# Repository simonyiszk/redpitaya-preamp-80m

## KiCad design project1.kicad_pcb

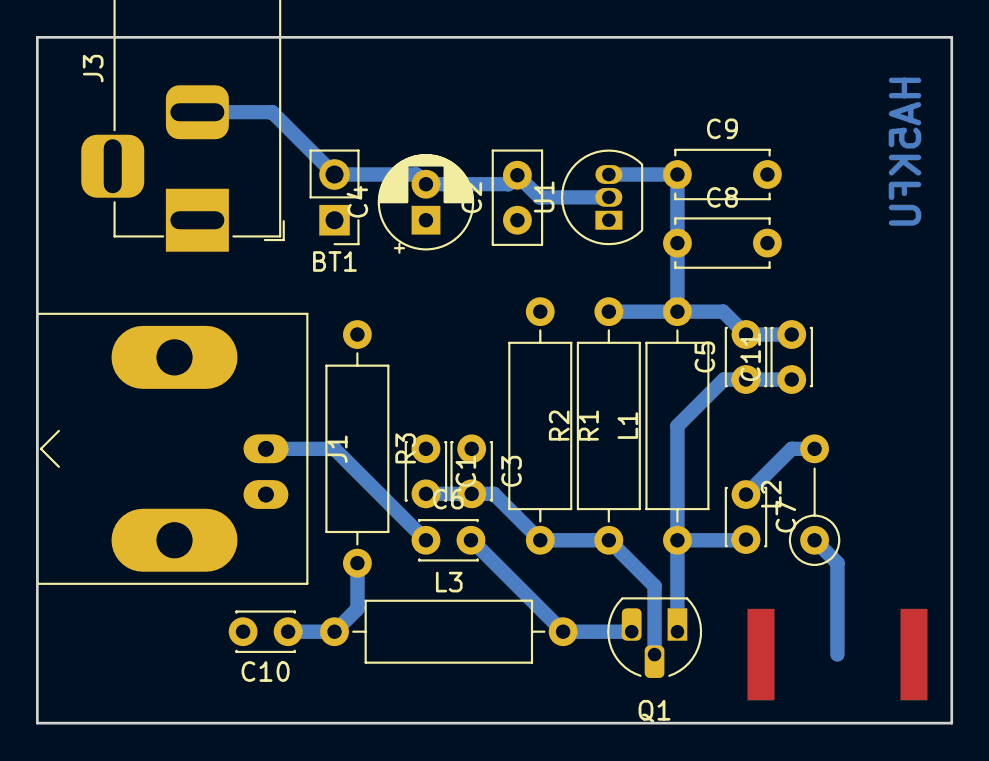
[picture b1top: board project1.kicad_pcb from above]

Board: 2 copper layers, 50.8 x 38.1 mm, 23 parts (1 on the bottom side), 10 nets.

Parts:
BT1: Battery_Cell; PinHeader_1x02_P2.54mm_Vertical
C1, C3, C6, C7: 8n2; C_Disc_D3.0mm_W2.0mm_P2.50mm
C2: 100n; C_Disc_D5.0mm_W2.5mm_P2.50mm
C4: 10u; CP_Radial_D5.0mm_P2.00mm
C5: 270p; C_Disc_D3.0mm_W2.0mm_P2.50mm
C8: 100n; C_Disc_D5.0mm_W2.5mm_P5.00mm
C9: 10n; C_Disc_D5.0mm_W2.5mm_P5.00mm
C10: C; C_Disc_D3.0mm_W2.0mm_P2.50mm
C11: 33p; C_Disc_D3.0mm_W2.0mm_P2.50mm
J1: Conn_Coaxial; BNC_Amphenol_B6252HB-NPP3G-50_Horizontal
J2: Conn_Coaxial; SMA_Amphenol_132289_EdgeMount
J3: Jack-DC; BarrelJack_Horizontal
L1: 6.3u; R_Axial_DIN0309_L9.0mm_D3.2mm_P12.70mm_Horizontal
L2: 62u; R_Axial_DIN0207_L6.3mm_D2.5mm_P5.08mm_Vertical
L3: L; R_Axial_DIN0309_L9.0mm_D3.2mm_P12.70mm_Horizontal
Q1: BC415; TO-92_HandSolder
R1: 51k; R_Axial_DIN0309_L9.0mm_D3.2mm_P12.70mm_Horizontal
R2: 38k; R_Axial_DIN0309_L9.0mm_D3.2mm_P12.70mm_Horizontal
R3: 8.8k; R_Axial_DIN0309_L9.0mm_D3.2mm_P12.70mm_Horizontal
U1: L7905; TO-92_Inline

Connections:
-9V: C5.2, C8.1, C9.1, C11.2, L1.2, R2.2, U1.3
GND: BT1.1, C1.1, C2.1, C3.1, C4.1, C8.2, C9.2, C10.2, J1.2, J2.2, J3.1, R1.1, R3.1, U1.1
unnamed: BT1.2, C2.2, C4.2, J3.2, U1.2
unnamed: C1.2, C3.2, Q1.2, R1.2, R2.1
unnamed: C6.1, J1.1
unnamed: C6.2, L3.2, Q1.3
unnamed: C7.1, L2.2
unnamed: C10.1, L3.1, R3.2
unnamed: C5.1, C7.2, C11.1, L1.1, Q1.1
unnamed: J2.1, L2.1

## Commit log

2019-11-26 Initial commit 2
